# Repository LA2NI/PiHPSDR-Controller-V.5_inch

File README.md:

# PiHPSDR-Controller-V.5_inch
I have done a new layout of PiHPSDR Controller V2 using a 5 inch capacitive LCD display. It has the same interface as the original 7 inch display (not HDMI) It can be installed in a Hammond extruded enclosure type 1455Q2202BK. I am looking for another enclosure that can be used to make a complete transceiver in the same box using Hermes/ Orion MK2 or Oddysevs MK2 together with a PA and LPF/HPF and ATU.
There are 2 versions of the schematics and Gerber files. The latest version is with the possibility to use the Chineese rotary encoder (or the HRPG-ASCA#) I strongly advice to use the Chineese one!
The software used is found https://github.com/g0orx?tab=repositories 
I am working with the BOM for this controller.
The .fpd file can be opened by Front Panel Designer

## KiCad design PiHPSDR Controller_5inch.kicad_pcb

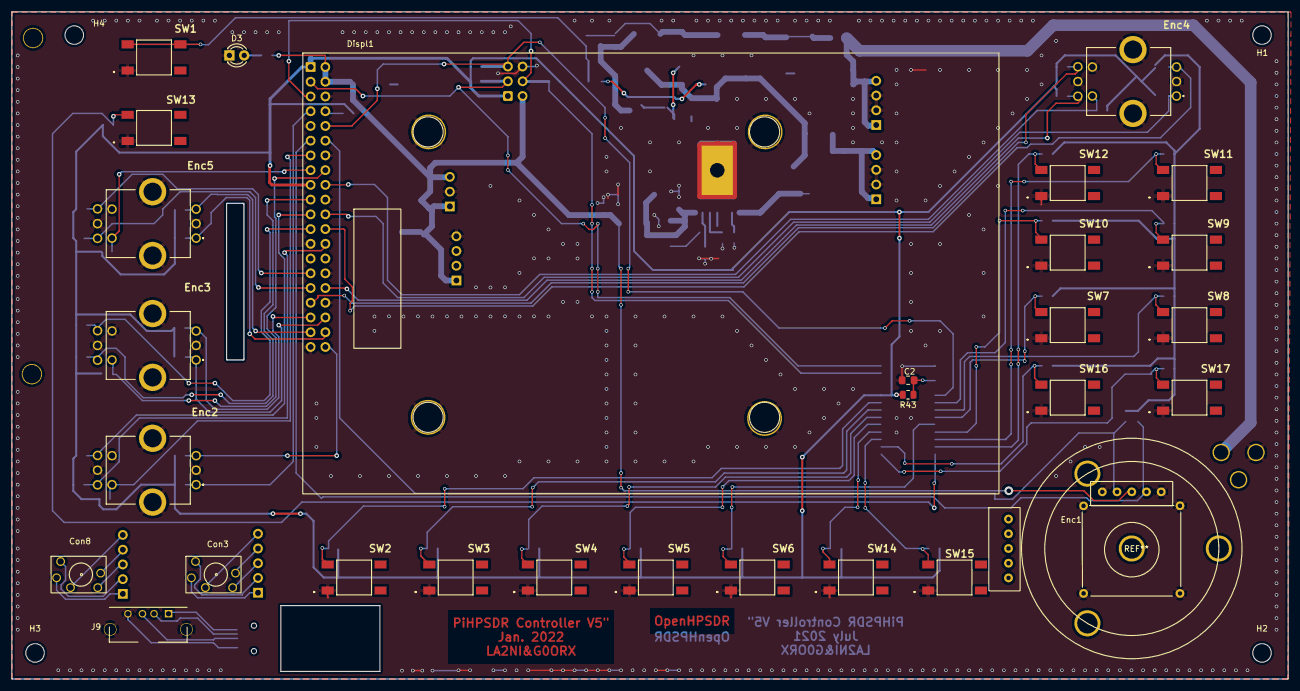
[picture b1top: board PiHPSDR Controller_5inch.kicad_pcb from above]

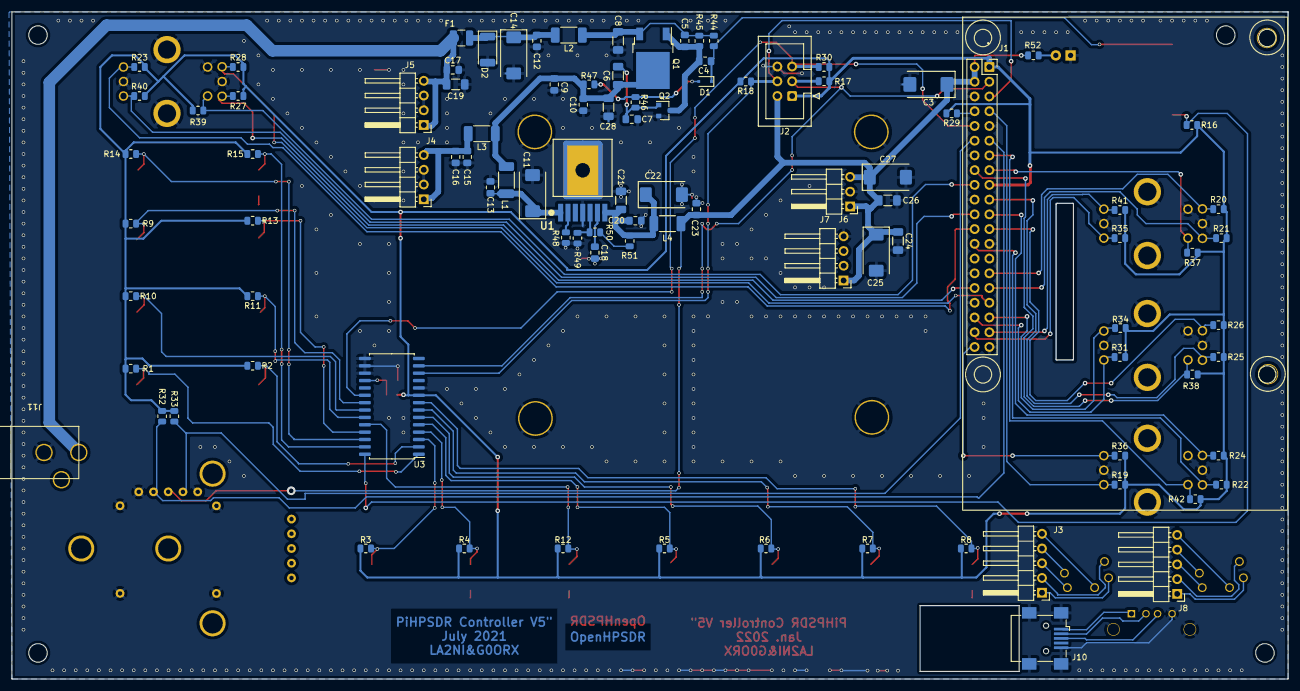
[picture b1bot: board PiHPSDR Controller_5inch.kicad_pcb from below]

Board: 2 copper layers, 220.0 x 115.0 mm, 131 parts (98 on the bottom side), 75 nets.

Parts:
C2: 1N; C_0805_2012Metric_Pad1.15x1.40mm_HandSolder
C3: CP; CP_EIA-7343-43_Kemet-X_Pad2.25x2.55mm_HandSolder
C4, C10, C15, C23: 1u; C_0805_2012Metric_Pad1.15x1.40mm_HandSolder
C5, C7, C9, C12, C13, C16, C17: 100n; C_0805_2012Metric_Pad1.15x1.40mm_HandSolder
C6: 4,7u; C_1206_3216Metric_Pad1.33x1.80mm_HandSolder
C8, C19, C21, C24, C26, C28: 10u; C_1206_3216Metric_Pad1.33x1.80mm_HandSolder
C11: 47u/35V; CP_EIA-7343-43_Kemet-X
C14: 22u/35V; CP_EIA-7343-43_Kemet-X
C18: 0,47u; C_0805_2012Metric_Pad1.15x1.40mm_HandSolder
C20: 1oon; C_0805_2012Metric_Pad1.15x1.40mm_HandSolder
C22, C25: 100u/10V; CP_EIA-7343-43_Kemet-X
C27: 100u/6,3V; CP_EIA-7343-43_Kemet-X
Con3, Con8: STX-3790-5N; Kycon_STX
D1: BAT54J; D_SOD-323F
D2: SK54; D_2010_5025Metric
D3: 3mm/GN; LED_D3.0mm_Clear
Displ1: Display_KeDei; KeDay 5 inch for RPi
Enc1: HRPG-ASCA#; HRPG_ASCA#
Enc2, Enc3, Enc4, Enc5: EC11EBB24C03
F1: 5a; Fuse_1210_3225Metric
H1, H2, H3, H4: MountingHole; MountingHole_3.2mm_M3
J1: Raspberry_Pi_2_3; Raspberry Pi_4
J2: Conn_02x03_Odd_Even; IDC-Header_2x03_P2.54mm_Vertical
J3, J8: Conn_01x05_Male; PinHeader_1x05_P2.54mm_Horizontal
J4, J5, J6: Conn_01x04_Male; PinHeader_1x04_P2.54mm_Horizontal
J7: Conn_01x03_Male; PinHeader_1x03_P2.54mm_Horizontal
J9: USB_A_Wurth; USB_A_Wurth_614004135023_Vertical
J10: USB_B_Mini_Wurth; USB_Mini-B_Wuerth_65100516121_Horizontal
J11: KLDX-0202; KLDX-0202A
L1, L2, L3, L4: L_Core_Ferrite_Small; L_2010_5025Metric_Pad1.52x2.65mm_HandSolder
Q1: FDD6685; TO-252-2
Q2: 2N7002K; SOT-23
R1, R2, R3, R4, R5, R6, R7, R8, R9, R10, R11, R12, R13, R14, R15, R16, R17, R18, R19, R20, R21, R23, R24, R25, R26, R27, R28, R29, R30, R31, R32, R33, R34, R35, R36, R37, R38, R39, R40, R41, R42, R44, R45: 10k; R_0805_2012Metric
R22: R; R_0805_2012Metric
R43: 100K; R_0805_2012Metric
R46: 180k; R_0805_2012Metric
R47: 100k; R_0805_2012Metric
R48, R52: 1,5k; R_0805_2012Metric
R49: 620R; R_0805_2012Metric
R50: 3,3k; R_0805_2012Metric
R51: 47R; R_0805_2012Metric
SW1, SW2, SW3, SW4, SW5, SW6, SW7, SW8, SW9, SW10, SW11, SW12, SW13, SW14, SW15, SW16, SW17: TL3301SPF260QG
U1: LMZ22005TZ_NOPB; NDW0007A
U3: MCP23017_SO; SOIC-28W_7.5x17.9mm_P1.27mm

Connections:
+3V3: J1.1 (3V3), J1.17 (3V3), J2.1, R1.2, R2.2, R3.2, R4.2, R5.2, R6.2, R7.2, R8.2, R9.2, R10.2, R11.2, R12.2, R13.2, R14.2, R15.2, R16.2, R17.2, R18.2, R19.2, R20.2, R21.2, R22.2, R23.2, R24.2, R25.2, R26.2, R27.2, R28.2, R29.2, R30.2, R31.2, R32.2, R33.2, R34.2, R35.2, R36.2, R37.2, R38.2, R39.2, R40.2, R41.2, R42.2, R43.1, U3.9 (VDD)
+5V: C3.1, C23.1, C24.1, C25.1, C26.1, C27.1, Enc1.3 (VCC), J1.2 (5V), J1.4 (5V), J2.2, J6.1, J7.1, J7.3, L4.2, R52.1
+12L: C5.1, C8.1, L2.1, Q1.3 (S), R44.1, R45.1
+12VA: C6.1, C9.1, C10.1, C28.1, L1.1, L3.1, Q1.2 (D), R47.1
/GPA0: R9.1, SW9.3, U3.21 (GPA0)
/GPA1: R10.1, SW8.3, U3.22 (GPA1)
/GPA2: R11.1, SW7.3, U3.23 (GPA2)
/GPA3: R12.1, SW6.3, U3.24 (GPA3)
/GPA4: R13.1, SW10.3, U3.25 (GPA4)
/GPA5: R14.1, SW11.3, U3.26 (GPA5)
/GPA6: R15.1, SW12.3, U3.27 (GPA6)
/GPA7: R16.1, SW13.3, U3.28 (GPA7)
/GPB0: R1.1, SW17.3, U3.1 (GPB0)
/GPB1: R2.1, SW16.3, U3.2 (GPB1)
/GPB2: R3.1, SW15.3, U3.3 (GPB2)
/GPB3: R4.1, SW14.3, U3.4 (GPB3)
/GPB4: R5.1, SW5.3, U3.5 (GPB4)
/GPB5: R6.1, SW4.3, U3.6 (GPB5)
/GPB6: R7.1, SW3.3, U3.7 (GPB6)
/GPB7: R8.1, SW2.3, U3.8 (GPB7)
/GPIO2: J1.3 (SDA/GPIO2), J2.3, R17.1, U3.13 (SDA)
/GPIO3: J1.5 (SCL/GPIO3), J2.4, R18.1, U3.12 (SCK)
/GPIO4: Enc2.A1, J1.7 (GCLK0/GPIO4), R19.1
/GPIO5: Enc5.B2, J1.29 (GCLK1/GPIO5), R20.1
/GPIO6: Enc5.A2, J1.31 (GCLK2/GPIO6), R21.1
/GPIO7: Enc2.A2, J1.26 (~CE1~/GPIO7), R22.1
/GPIO8: Enc4.B1, J1.24 (~CE0~/GPIO8), R23.1
/GPIO9: Enc2.B2, J1.21 (MISO0/GPIO9), R24.1
/GPIO10: Enc3.A2, J1.19 (MOSI0/GPIO10), R25.1
/GPIO11: Enc3.B2, J1.23 (SCLK0/GPIO11), R26.1
/GPIO12: Enc4.A2, J1.32 (PWM0/GPIO12), R27.1
/GPIO13: Enc4.B2, J1.33 (PWM1/GPIO13), R28.1
/GPIO14: J1.8 (GPIO14/TXD), R29.1
/GPIO15: J1.10 (GPIO15/RXD), J2.5, R30.1, U3.20 (INTA)
/GPIO16: Enc3.A1, J1.36 (GPIO16), R31.1
/GPIO17: Enc1.4 (A), J1.11 (GPIO17), R32.1
/GPIO18: Enc1.2 (B), J1.12 (GPIO18/PWM0), R33.1
/GPIO19: Enc3.B1, J1.35 (GPIO19/MISO1), R34.1
/GPIO20: Enc5.A1, J1.38 (GPIO20/MOSI1), R35.1
/GPIO21: Enc2.B1, J1.40 (GPIO21/SCLK1), R36.1
/GPIO22: Enc5.D1, J1.15 (GPIO22), R37.1
/GPIO23: Enc3.D1, J1.16 (GPIO23), R38.1
/GPIO24: Enc4.D1, J1.18 (GPIO24), R39.1
/GPIO25: Enc4.A1, J1.22 (GPIO25), R40.1
/GPIO26: Enc5.B1, J1.37 (GPIO26), R41.1
/GPIO27: Enc2.D1, J1.13 (GPIO27), R42.1
GND: C2.2, C3.2, C7.2, C8.2, C9.2, C10.2, C11.2, C12.2, C13.2, C14.2, C15.2, C16.2, C17.2, C18.2, C19.2, C20.2, C21.2, C22.2, C23.2, C24.2, C25.2, C26.2, C27.2, C28.2, D2.2 (A), D3.1 (K), Displ1.1, Displ1.2, Displ1.3, Displ1.4, Enc1.1 (GND), Enc1.5 (GND), Enc1.6 (GND), Enc1.7 (GND), Enc1.8 (gnd), Enc1.9 (gnd), Enc2.C1, Enc2.C2, Enc2.E1, Enc2.MH1, Enc2.MH2, Enc3.C1, Enc3.C2, Enc3.E1, Enc3.MH1, Enc3.MH2, Enc4.C1, Enc4.C2, Enc4.E1, Enc4.MH1, Enc4.MH2, Enc5.C1, Enc5.C2, Enc5.E1, Enc5.MH1, Enc5.MH2, J1.6 (GND), J1.9 (GND), J1.14 (GND), J1.20 (GND), J1.25 (GND), J1.30 (GND), J1.34 (GND), J1.39 (GND), J2.6, J4.2, J4.3, J5.2, J5.3, J6.4, J7.2, J9.4 (GND), J9.5 (Shield), J9.6 (GND), J10.5, J10.6, J10.7, J10.8, J10.9, J11.2, Q2.2 (S), R48.2, R49.2, SW1.1, SW2.1, SW3.1, SW4.1, SW5.1, SW6.1, SW7.1, SW8.1, SW9.1, SW10.1, SW11.1, SW12.1, SW13.1, SW14.1, SW15.1, SW16.1, SW17.1, U1.4 (AGND), U1.8 (PGND/EP), U3.10 (VSS), U3.15 (A0), U3.16 (A1), U3.17 (A2)
unnamed: C2.1, R43.2, U3.18 (~RESET~)
unnamed: C4.1, D1.1 (K), R44.2, SW1.3, SW1.4
unnamed: C4.2, C5.2, Q1.1 (G), Q2.3 (D), R45.2
unnamed: C6.2, C7.1, Q2.1 (G), R46.1
unnamed: C11.1, C13.1, L1.2, U1.1 (VIN)
unnamed: C12.1, C14.1, D2.1 (K), F1.1, L2.2
unnamed: C15.1, C16.1, J4.1, J4.4, L3.2
unnamed: C17.1, C19.1, F1.2, J5.1, J5.4, J11.1
unnamed: C18.1, U1.6 (SS/TRK)
unnamed: C20.1, C21.1, C22.1, L4.1, R51.2, U1.7 (VOUT)
unnamed: Con3.1, J3.1
unnamed: Con3.2, J3.2
unnamed: Con3.3, J3.3
unnamed: Con3.4, J3.4
unnamed: Con3.5, J3.5
unnamed: Con8.1, J8.1
unnamed: Con8.2, J8.2
unnamed: Con8.3, J8.3
unnamed: Con8.4, J8.4
unnamed: Con8.5, J8.5
unnamed: D1.2 (A), R46.2, R47.2
unnamed: D3.2 (A), R52.2
unnamed: J9.1 (VBUS), J10.1 (VBUS)
unnamed: J9.2 (D-), J10.2 (D-)
unnamed: J9.3 (D+), J10.3 (D+)
unnamed: R48.1, U1.2 (SYNC)
unnamed: R49.1, R50.1, U1.5 (FB)
unnamed: R50.2, R51.1

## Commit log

2021-07-10 Create README.md
    I have done a new layout of the PiHPSDR Controller V.2. The original controller use a 7 inch Touch Display (the original one made for Raspberry Pi). The new 5 inch version use a KeDei 5 inch 800x480 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
2021-07-12 Add .circleci/config.yml
